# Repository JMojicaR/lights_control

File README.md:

# Staircase Light Controller — ESP32-S3 (mmWave radar + BH1750)

Automatically controls a 5V LED strip on a staircase using **HLK-LD2410B/C
mmWave radar** for presence detection, a **BH1750** ambient-light sensor, and
time-of-day logic (sunset API). Includes a **web dashboard** for live monitoring
and manual override.

> This is the **`uart_option`** variant. The radars detect a person who is
> **completely still** (micro-motion) — the key advantage over PIR — and they
> connect over simple digital lines instead of the old I²C ToF bus, so they can
> sit **tens of metres** from the controller over cheap **Cat6** cable.

## How It Works

```
Person on stairs?  ──┐
It's dark?          ──┤──▶ All 3 true? ──▶ LIGHTS ON
Past sunset?        ──┘

Any condition false ────────────────▶ LIGHTS OFF (after timeout)
```

**Decision logic:**
1. **mmWave radar OUT pin** (bottom + top of stairs) — HIGH when a person is
   present, moving **or stationary**. No I²C bus, no address collision, no
   pull-up tuning.
2. **BH1750** measures ambient light (lux) — ensures lights don't fire in daylight.
3. **sunrise-sunset.org API** provides sunset time — lights only at night.
4. Lights stay ON for a configurable duration (default 90 s), then fade OFF.
   A motion debounce (default 2 s) ignores re-triggers while the lights are on.
5. **Manual override** via web dashboard — force ON / OFF / AUTO.

Presence is read by polling each radar's OUT pin (debounced). The radar UART
also carries **configuration commands** — the sensing distance (detection range)
is set live from the dashboard via the radar's max-distance gate. The BH1750 is
polled (**5 s by default**, configurable), since lux changes slowly.

### Why mmWave radar instead of PIR?

| Feature | HC-SR501 PIR | HLK-LD2410B/C mmWave |
|---------|-------------|----------------------|
| Detection method | Passive infrared (heat movement) | 24 GHz radar (micro-motion) |
| Still person | ❌ Not detected | ✅ Detected |
| Hot environments | ❌ Fails (ambient ≈ body temp) | ✅ Works |
| Output | Binary (HIGH/LOW) | Binary OUT **+** UART distance |
| Range | ~5 m cone | Up to ~6 m, configurable |
| Interface | Single digital pin | OUT pin + UART (256 kbps) |
| Configurability | Fixed | Sensitivity/gates via HLK app or UART |

It also replaces the earlier **VL53L0X ToF** approach: the ToF needed a shared
I²C bus (address re-mapping + ~3 m cable ceiling), while the radar's push-pull
digital lines run 15–30 m with no extra hardware.

## Sensors & Specifications

### HLK-LD2410B / LD2410C — 24 GHz mmWave presence radar (×2)

| Parameter | Value |
|-----------|-------|
| Frequency | 24 GHz mmWave |
| Presence | **OUT** pin HIGH = person present (moving **or** stationary) |
| Supply | **5 V DC** (not 3.3 V) |
| Current | ~80–100 mA typical |
| Logic level | 3.3 V push-pull (OUT) |
| UART | 256 000 baud, 8N1 (distance + configuration) |
| Detection range | up to ~6 m, configurable (HLK app / UART) |
| OUT interface | Single digital pin |

**LD2410C vs LD2410B:** the **LD2410C** is a drop-in replacement — same OUT pin,
same UART protocol (256 kbps), same 5 V power — but adds **built-in BLE** for
configuration from the phone app and breadboard-friendly 2.54 mm pins.
**Verify the pin order** on the silkscreen, it can differ between B and C.

### BH1750 — ambient light sensor

| Parameter | Value |
|-----------|-------|
| Interface | I²C, address **0x23** |
| Output | Real lux (no calibration) |
| Mode | CONTINUOUS_HIGH_RES_MODE |
| Placement | **< 30 cm** from the ESP32 (short I²C — no pull-up/length tuning) |
| Wiring | SDA **GPIO 12**, SCL **GPIO 13** |

## Web Dashboard

Open `http://<esp32-ip>/` in any browser on the same network.

| Tile | Description |
|------|-------------|
| **Live status** | Lights ON/OFF, ambient lux, **motion location (bottom/top)**, local time, sunset |
| **Manual override** | Force ON, Force OFF, or return to AUTO mode |
| **Uptime & RSSI** | Device uptime and WiFi signal strength |
| **Duration / Poll / Sensing** | Set light duration (s), ambient-light (BH1750) polling interval (s), and radar **sensing distance (cm)** — all persisted to NVS |
| **JSON API** | `GET /api` returns machine-readable JSON |
| **Override API** | `GET /api/override?mode=on\|off\|auto` |
| **Duration API** | `POST /api/duration?seconds=N` |
| **Poll API** | `POST /api/poll?seconds=N` |
| **Sensing API** | `POST /api/sensing?cm=N` — sets the radar detection range live |
| **Auto-refresh** | Dashboard polls every 2 seconds |

> The dashboard shows **where motion was detected** (bottom / top) rather than
> the radar's distance reading. The radar's sensing distance is now changed from
> the dashboard (it sends a UART config command to the radar's max-distance gate).

### API Examples

```bash
curl http://192.168.1.42/api
# → {"lights_on":false,"duty":0,"lux":3.5,"presence_bottom":true,"presence_top":false,
#    "motion_bottom":true,"motion_top":false,"sensing_distance_cm":600,
#    "time":"14:30","sunset":"19:15",...}

curl "http://192.168.1.42/api/override?mode=on"    # → {"override":"on","lights_on":true}
curl "http://192.168.1.42/api/override?mode=auto"  # → {"override":"auto","lights_on":false}

curl -X POST "http://192.168.1.42/api/duration?seconds=120"  # set light duration
curl -X POST "http://192.168.1.42/api/poll?seconds=10"        # set BH1750 poll interval
```

## Hardware

| Component | Purpose | Pins |
|-----------|---------|------|
| ESP32-S3 SuperMini | Controller | — |
| HLK-LD2410B/C radar (bottom) | Presence detection | OUT → GPIO 4, TX → GPIO 7 (RX) |
| HLK-LD2410B/C radar (top) | Presence detection | OUT → GPIO 6, TX → GPIO 8 (RX) |
| BH1750 | Ambient light sensor | I²C SDA 12, SCL 13 |
| IRLZ44N MOSFET | Switch 5 V LED strip (low-side) | Gate → GPIO 5 |
| 5 V LED strip (USB-A plug) | Staircase lighting | USB-A port (switched GND) |
| 5 V 2 A USB charger | Powers everything (ESP32 + radars + strip) | — |

### Wiring (pin-by-pin)

```
ESP32-S3               Peripheral
────────               ──────────
GPIO 4   ───────────── Radar BOTTOM OUT   (presence, HIGH = present)
GPIO 7   ───────────── Radar BOTTOM TX    (UART RX ← radar, 256000 baud)
GPIO 9   ───────────── Radar BOTTOM RX    (UART TX → radar, config commands)
GPIO 6   ───────────── Radar TOP OUT
GPIO 8   ───────────── Radar TOP TX       (UART RX ← radar, 256000 baud)
GPIO 10  ───────────── Radar TOP RX       (UART TX → radar, config commands)
GPIO 12  ───────────── BH1750 SDA
GPIO 13  ───────────── BH1750 SCL
GPIO 5   ──[10 kΩ]──┬─ IRLZ44N GATE   (10 kΩ pulldown to GND keeps it OFF at boot)
                    └─ GND
5 V      ───────────── Radar VCC (×2)   ← NOT the ESP32 3V3 pin
3.3 V    ───────────── BH1750 VCC
GND      ───────────── Radar GND (×2), BH1750 GND

5 V USB (+) ──┬── ESP32 5 V pin
              ├── Radar VCC (×2)
              └── LED strip (+)      (USB-A VBUS)
LED strip (−) ─── IRLZ44N DRAIN      (USB-A GND, low-side switched)
IRLZ44N SOURCE ─── GND (common)
```

## Electrical & Wiring Considerations (Cat6 / Ethernet cable)

The radar `OUT` and `UART` lines are **3.3 V push-pull digital** — no I²C
open-drain/400 pF ceiling — so they run far longer than the old ToF bus.

### Distance limits

| Signal | Type | Comfortable | Max (with care) |
|--------|------|-------------|-----------------|
| Radar **OUT** (presence) | digital, slow | **20–30 m** | 50 m+ |
| Radar **UART** (256 kbps) | digital, push-pull | **15–20 m** | 30 m+ (lower baud) |

> **Staircase reality check:** top/bottom radars are at most ~5 m from a central
> ESP32 — well inside the comfort zone.

### Use Cat6 (or Cat5e) — one cable per radar

Cat6 gives you twisted pairs for free (each signal twisted with a GND return),
which is exactly what rejects EMI on a 15–30 m digital run.

| Factor | Cat6 | Separate 24 AWG |
|--------|------|-----------------|
| Noise immunity | ✅ 4 twisted pairs | ❌ must twist by hand |
| Conductors | ✅ 8 wires | buy 4+ strands |
| Gauge / power | ✅ 23 AWG solid (low 5 V drop) | 24 AWG (higher resistance) |
| Cost / convenience | ✅ one cable | multiple rolls |

### Per-radar Cat6 pair assignment

| Pair | Colour | Signals | Purpose |
|------|--------|---------|---------|
| 1 | orange | VCC (5 V) + GND | power |
| 2 | green | OUT + GND | presence |
| 3 | blue | TX + GND | UART distance |
| 4 | brown | RX + GND | spare (future config) |

### Power & electrical notes

- Radars run on **5 V** (not 3.3 V) — never feed them from the ESP32's 3V3 pin.
- At 20 m of 23 AWG the 5 V drop at ~80–100 mA is negligible (~0.15 V). For
  > 30 m, run 12 V and regulate to 5 V **at each radar**.
- UART at 256 kbps is trivial over 30 m; drop to 115200/9600 for noisy long runs.
- One **5 V / 2 A USB charger** feeds everything: strip 1–1.5 A + 2 radars ≈0.2 A
  + ESP32 ≈0.15 A ≈ 1.85 A max (within 2 A). Star-ground at one point.
- The MOSFET gate needs a **10 kΩ pulldown to GND** so the strip stays off while
  the ESP32 boots.
- **LD2410C is drop-in** for LD2410B (same OUT + UART + protocol); check the pin
  order on the silkscreen — it can differ between B and C.

## APIs Used

| API | Endpoint | Purpose | Key Required? |
|-----|----------|---------|---------------|
| timeapi.io | `timeapi.io/api/v1/time/current/zone?timezone={tz}` | Current time + timezone | No |
| sunrise-sunset.org | `api.sunrise-sunset.org/json` | Sunset/sunrise times | No |

## Configuration

Edit `config.h` before flashing:

```cpp
#define WIFI_SSID       "YOUR_SSID"
#define WIFI_PASSWORD   "YOUR_PASSWORD"
#define LATITUDE        19.4326    // Your location
#define LONGITUDE       -99.1332
#define TIMEZONE        "America/Mexico_City"

#define RADAR_BOTTOM_PIN   4     // bottom radar OUT → GPIO 4
#define RADAR_TOP_PIN      6     // top radar OUT    → GPIO 6
#define LED_MOSFET_PIN     5     // IRLZ44N gate
#define I2C_SDA            12    // BH1750 SDA
#define I2C_SCL            13    // BH1750 SCL

#define RADAR_UART_BAUD    256000
#define RADAR_BOTTOM_RX    7     // ESP32 RX ← bottom radar TX
#define RADAR_TOP_RX       8     // ESP32 RX ← top radar TX

#define LUX_THRESHOLD      30    // lux below this = "dark enough"
#define DEFAULT_LIGHT_DURATION_SEC  90
#define MOTION_DEBOUNCE_MS  2000  // ignore re-triggers within this window
#define POLL_INTERVAL_DEFAULT_SEC  5
```

Light duration, the BH1750 polling interval, and the radar sensing distance
(detection range) can be changed live from the dashboard (persisted to NVS,
survive reboot). The sensing distance is applied by sending a UART config
command to each radar's max-distance gate.

## Build & Flash

```bash
arduino-cli lib install BH1750
arduino-cli lib install ArduinoJson

arduino-cli compile --fqbn esp32:esp32:esp32s3 .
arduino-cli upload -p /dev/ttyUSB0 --fqbn esp32:esp32:esp32s3 .
arduino-cli monitor -p /dev/ttyUSB0 -c baudrate=115200
```

## Serial Output

```
=== Staircase Light Controller ===
[✓] Radar bottom OUT on GPIO 4
[✓] Radar top OUT on GPIO 6
[✓] BH1750 ready
[✓] WiFi connected — IP: 192.168.1.42
[🌐] Dashboard: http://192.168.1.42/
--- Ready ---
[STATUS] 14:30:15 | Lux: 450 | Bottom: 2100mm | Top: 2050mm | Lights: OFF | Sunset: 19:15 | Mode: AUTO
[👣] Presence detected — bottom! (450 mm)
[💡] Decision: ON  (presence=1 dark=1 night=1 lux=3)
[💡] Lights → ON (fading in)
```

## Dependencies (Arduino Libraries)

| Library | Version | Install |
|---------|---------|---------|
| BH1750 | ≥1.3.0 | `arduino-cli lib install BH1750` |
| ArduinoJson | ≥7.0 | `arduino-cli lib install ArduinoJson` |

WiFi, HTTPClient, Wire, and WebServer are included with the ESP32 board package.
(No VL53L0X library — that sensor was replaced by the mmWave radars.)

## Enclosure Models

FreeCAD (.FCStd) models are in `enclosures/`:

| File | Description |
|------|-------------|
| `enclosures/main_box.FCStd` | Main controller enclosure (ESP32-S3 + MOSFET + terminals) |
| `enclosures/sensor_bottom.FCStd` | Radar housing — bottom of stairs |
| `enclosures/sensor_top.FCStd` | Radar housing — top of stairs |
| `enclosures/bh1750_housing.FCStd` | BH1750 ambient-light sensor housing |

Print in PETG or ABS for heat resistance (PLA may warp near the MOSFET).

## Other docs (this branch)

- `docs/distance_and_wiring.md` — distance limits + exact connection diagram + Cat6 pair assignment
- `docs/BOM_UART.md` — bill of materials
- `docs/UART_schematic.svg` — schematic
- `docs/cost_roi_UART.md` + `docs/market_analysis_UART.md` / `.pdf` — cost, ROI & market analysis (DIY kit)

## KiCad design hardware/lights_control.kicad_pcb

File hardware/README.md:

# Hardware — Controller PCB (uart_option, 5V USB)

KiCad 10 schematic + PCB for the **lights_control `uart_option`** controller board:
ESP32-S3 SuperMini + 2× HLK-LD2410C mmWave radar (remote, via RJ45) + BH1750.

Everything runs from a single **5 V / 2 A USB phone charger** — no 12 V, no buck.

## Design

- **Modular / socketed**: the **ESP32-S3 SuperMini** sits in a **2×9 female
  header socket**, the **BH1750** in a **1×4 socket** — no direct solder.
- **2× RJ45 (8P8C)** jacks, one per remote LD2410C radar (Cat6 run carries
  5 V + GND + OUT + TX + RX over the four twisted pairs).
- **Power in**: a 2-pin terminal (**5V IN**) fed from the USB charger's 5 V rail
  (cut a USB cable, or use a USB-C breakout).
- **LED strip out**: a **USB-A female** receptacle — the strip's USB-A plug
  plugs straight in. The **IRLZ44N** MOSFET switches the strip **low-side**
  (its GND return), so the strip's VBUS stays tied to +5 V.
- **Status LED** on GPIO 2; screw terminals for power/strip.

### Power budget (5 V / 2 A)

| Load | Current |
|------|---------|
| LED strip | 1–1.5 A |
| 2× radar | ≈0.2 A |
| ESP32-S3 + BH1750 | ≈0.15 A |
| **Total (max)** | **≈1.85 A** (within 2 A) |

### RJ45 pin mapping (per radar, T568B pairs)

| RJ45 pin | Pair | Signal |
|----------|------|--------|
| 1 | orange | +5 V |
| 2 | orange | GND |
| 3 | green | OUT (presence) |
| 6 | green | GND |
| 4 | blue | TX (UART) |
| 5 | blue | GND |
| 7 | brown | RX (spare) |
| 8 | brown | GND |

### ESP32-S3 SuperMini pin usage

| SuperMini pin | Net |
|---------------|-----|
| 5V / GND / 3V3 | power |
| GPIO 2 | status LED |
| GPIO 4 | radar BOTTOM OUT |
| GPIO 6 | radar TOP OUT |
| GPIO 5 | MOSFET gate (10 kΩ pulldown) |
| GPIO 7 | radar BOTTOM TX |
| GPIO 8 | radar TOP TX |
| GPIO 9 / 10 | radar BOTTOM/TOP RX (config) |
| GPIO 12 / 13 | BH1750 SDA / SCL |

## Files

- `lights_control.kicad_pro` / `.kicad_sch` / `.kicad_pcb` — project, schematic, PCB
- `lights_control.kicad_sym` — custom symbols (SuperMini, BH1750, RJ45, USB-A, passives)
- `lights_control.pretty/` — custom footprints (sockets, RJ45, USB-A, THT passives)
- `lights_control_schematic.pdf` — rendered schematic
- `gerbers/` — full Gerber set + drill (JLCPCB-ready)
- `gen_kicad.py` — generator (regenerates all files)

## Regenerate

```bash
python3 gen_kicad.py
kicad-cli sch export pdf -o lights_control_schematic.pdf lights_control.kicad_sch
kicad-cli pcb export gerbers -o gerbers/ lights_control.kicad_pcb
kicad-cli pcb export drill -o gerbers/ lights_control.kicad_pcb
```

## Notes & assumptions

- **SuperMini pin order**: the 2×9 socket follows the standard 18 side-header
  pins (5V/GND/3V3 + GPIO1–13 + GPIO43/44). **Verify against your specific
  board's silkscreen** — ordering varies between manufacturers.
- **USB-A female** (strip): pin 1 = VBUS (+5 V), pin 4 = GND (switched to the
  MOSFET drain); pins 2/3 (D−/D+) unused. The strip is switched on its **GND
  return** (low-side), which is fine for a plain white strip with no data lines.
- **Unused pins** (SuperMini GPIO1/3/11–14/43/44, RJ45 shields, USB-A D±) are
  no-connect — the DRC "unconnected items" are expected.
- **Routing is a first-pass** (auto chain, GND on B.Cu, power 0.5 mm / signals
  0.25 mm). Review and tidy in the KiCad PCB editor before manufacturing.
- The **5V IN** terminal expects a clean 5 V; the USB charger's over-current
  protection is the only "fuse" — don't run a strip that pushes the total past
  2 A.

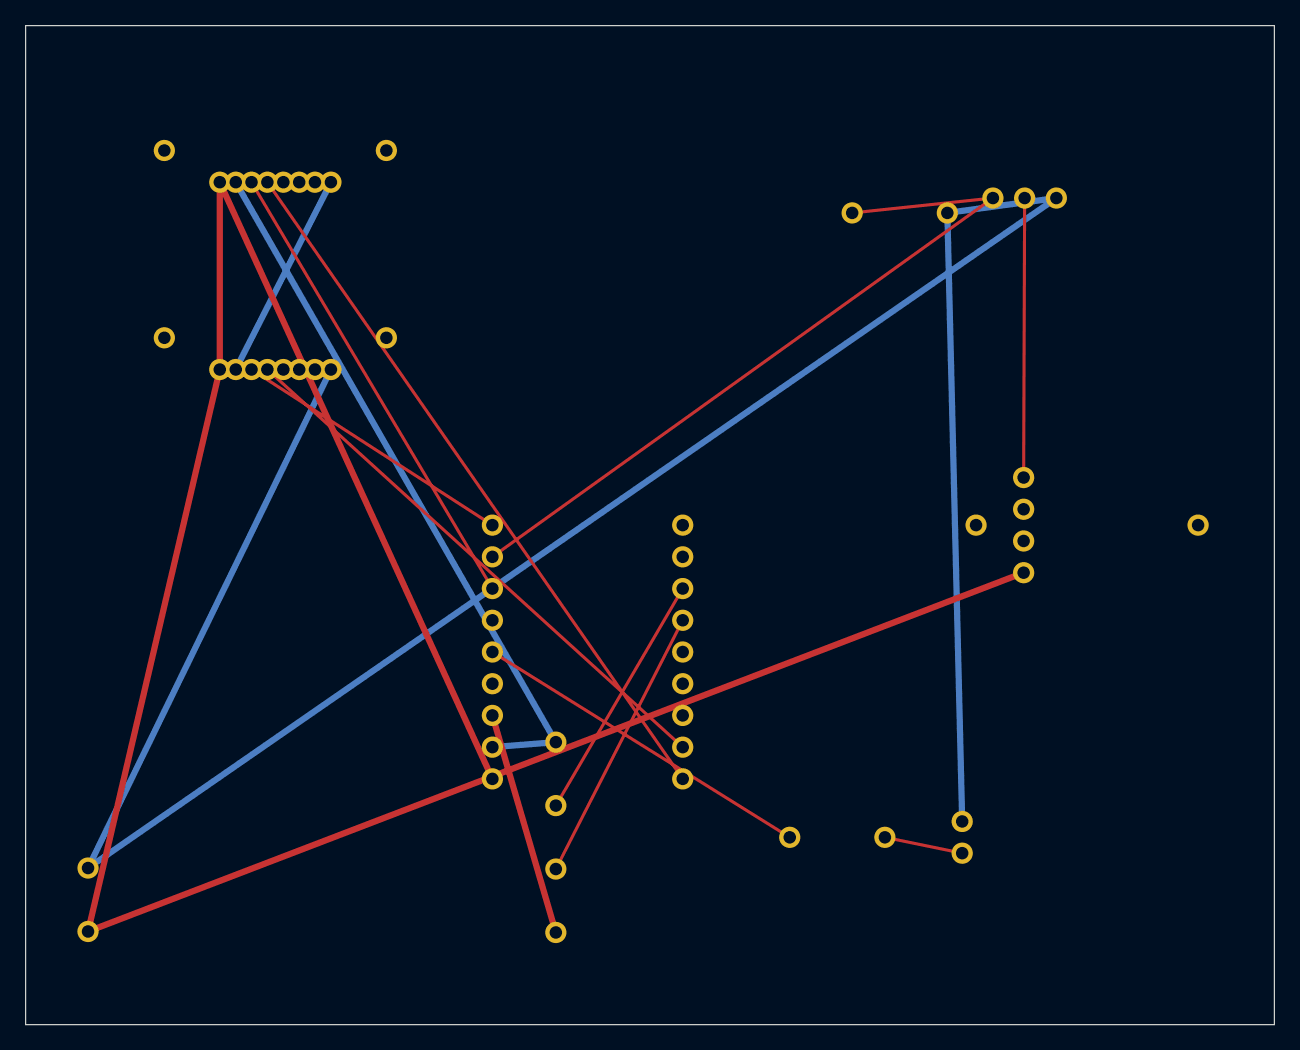
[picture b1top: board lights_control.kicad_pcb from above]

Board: 2 copper layers, 100.0 x 80.0 mm, 10 parts (0 on the bottom side), 13 nets.

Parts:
D1: STATUS; LED_5mm
J1: RJ45 BOTTOM; RJ45_8P8C
J2: RJ45 TOP; RJ45_8P8C
J3: 5V IN (USB); Terminal_1x02
J4: LED STRIP; USB_A_Female
Q1: IRLZ44N; TO220_3
R1: 10k; R_Axial
R2: 330; R_Axial
U1: ESP32-S3 SuperMini; SuperMini_S3_Socket
U3: BH1750; BH1750_1x04

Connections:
+3V3: U1.3, U3.1
+5V: J1.1, J2.1, J3.1, J4.1, U1.1
GND: D1.1, J1.2, J1.5, J1.6, J1.8, J2.2, J2.5, J2.6, J2.8, J3.2, Q1.3, R1.2, U1.2, U3.4
LED_A: D1.2, R2.2
LED_GATE: Q1.1, R1.1, U1.8
LED_STATUS: R2.1, U1.5
RADAR_BOTTOM_OUT: J1.3, U1.7
RADAR_BOTTOM_TX: J1.4, U1.10
RADAR_TOP_OUT: J2.3, U1.9
RADAR_TOP_TX: J2.4, U1.11
SCL: U1.16, U3.3
SDA: U1.15, U3.2
STRIP_MINUS: J4.4, Q1.2

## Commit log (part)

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2026-06-29 feat: initial commit — staircase light controller
    ESP32-S3 SuperMini with HC-SR501 PIR motion sensor, BH1750 ambient
    light sensor, and IRLZ44N MOSFET controlling 12V LED strip.
    - Motion + darkness + past-sunset logic
    - HTTP time sync via WorldTimeAPI
    - HTTP sunset sync via sunrise-sunset.org (free, no API key)
    - 2-minute light timeout after last motion
